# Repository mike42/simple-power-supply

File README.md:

# Simple power supply

This is a tiny linear power supply module which I use for breadboard-based electronics projects.

It is designed to sit on a desk, and may be assembled to deliver either a fixed 3.3V or 5V output.

## Parts list

| Qty. | Description                     | Installed at | Product ref.                                                                                 |
|------|---------------------------------|--------------|----------------------------------------------------------------------------------------------|
| 1    | 100µF electrolytic capacior     | C1           |                                                                                              |
| 1    | 0.1µF ceramic capacitor         | C2           | 		                                                                                         |
| 1    | 1N5819 diode                    | D1           | 	                                                                                           |
| 1    | 5mm LED                         | D2           | 	                                                                                           |
| 1    | Barrel jack                     | J1           | [Adafruit 373](https://au.mouser.com/ProductDetail/485-373)                                  |
| 3    | 2.54mm connector 1x2 male       | J2, J3, J4   | [Amphenol FCI 10129378-902001BLF](https://au.mouser.com/ProductDetail/649-1012937890201BLF)  |
| 1    | 1k resistor                     | R1           |                                                                                              |
| 1    | SPDT switch 2.54mm lead spacing | SW1          | [SparkFun COM-00102](https://au.mouser.com/ProductDetail/474-COM-00102)                      |
| 1    | L7805 Regulator                 | U1           | [STMicroelectronics L7805ABV](https://au.mouser.com/ProductDetail/511-L7805ABV)              |

## Licensing 

This work is licensed under the [Creative Commons Attribution 4.0 International License](https://creativecommons.org/licenses/by/4.0/).

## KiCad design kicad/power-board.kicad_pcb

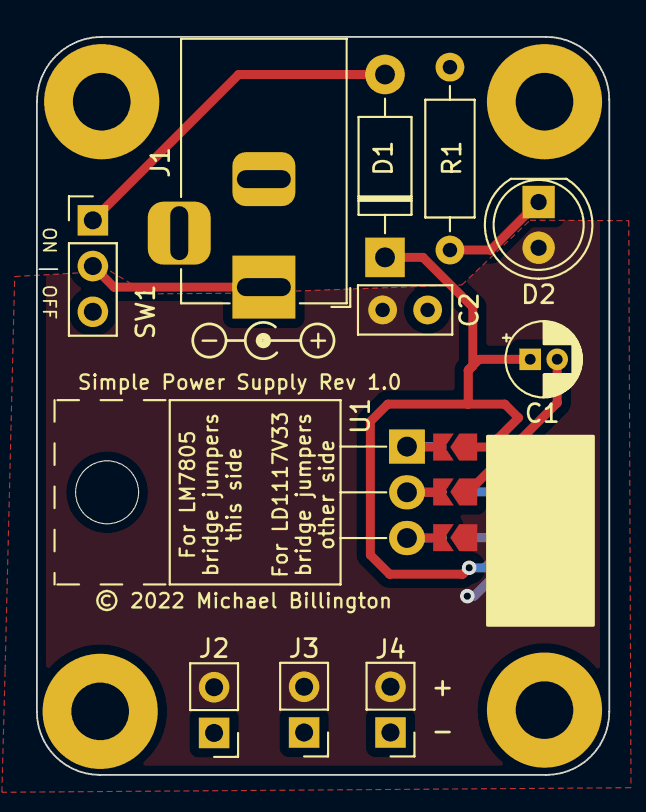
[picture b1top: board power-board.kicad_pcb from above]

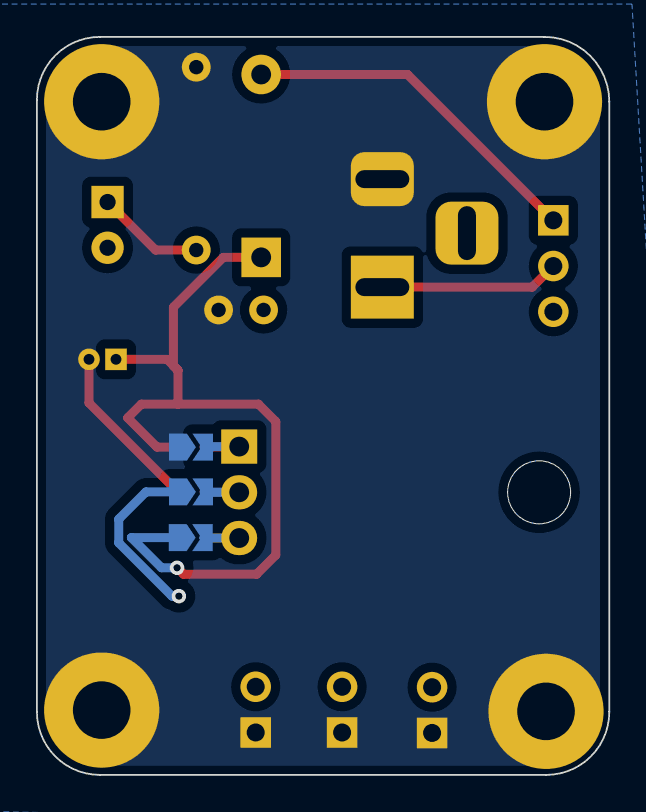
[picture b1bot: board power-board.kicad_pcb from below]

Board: 2 copper layers, 31.8 x 41.0 mm, 22 parts (3 on the bottom side), 9 nets.

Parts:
C1: 100µF; CP_Radial_D4.0mm_P1.50mm
C2: 0.1µF; C_Disc_D5.0mm_W2.5mm_P2.50mm
D1: 1N5819; D_DO-41_SOD81_P10.16mm_Horizontal
D2: LED; LED_D5.0mm
H1, H2, H3, H4: MountingHole_3.2mm_M3_Pad
H5: Symbol_Barrel_Polarity
J1: Barrel_Jack; BarrelJack_Horizontal
J2, J3, J4: Conn_01x02_Male; PinHeader_1x02_P2.54mm_Vertical
JP1, JP2, JP3, JP4, JP5, JP6: SolderJumper_2_Open; SolderJumper-2_P1.3mm_Open_TrianglePad1.0x1.5mm
R1: 1k; R_Axial_DIN0207_L6.3mm_D2.5mm_P10.16mm_Horizontal
SW1: SW_SPDT; PinHeader_1x03_P2.54mm_Vertical
U1: L7805; TO-220-3_Horizontal_TabUp

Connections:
/PWR_RAW: J1.1, SW1.2 (B)
/PWR_SW: D1.2 (A), SW1.1 (A)
/REG1: JP1.2 (B), JP4.2 (B), U1.1 (IN)
/REG2: JP2.2 (B), JP5.2 (B), U1.2 (GND)
/REG3: JP3.2 (B), JP6.2 (B), U1.3 (OUT)
/REG_IN: C1.1, D1.1 (K), JP1.1 (A), JP6.1 (A)
/REG_OUT: C2.1, D2.2 (A), J2.2, J3.2, J4.2, JP3.1 (A), JP5.1 (A)
GND: C1.2, C2.2, H1.1, H2.1, H3.1, H4.1, J1.2, J2.1, J3.1, J4.1, JP2.1 (A), JP4.1 (A), R1.2
unnamed: D2.1 (K), R1.1

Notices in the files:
kicad/power-board.kicad_pcb:
© 2022 Michael Billington
